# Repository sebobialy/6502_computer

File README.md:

# 6502_computer
Simple 6502 DIY computer for peripheral prototyping

**This is a work in progress. Do not try to manufacture yet.**
# Features
1. 65C02 with selectable speed
2. 6551 UART/ACIA with optional USB support via CH340N
3. 6840 clock chip (with buzzer attached)
4. CPU bus accessible, with several selection signals for various parts of memory
5. SyMon III directly working through UART/USB
6. Simple emulator
7. PCB with all possible markings, memory map, and values
8. Compact form, retro look&feel

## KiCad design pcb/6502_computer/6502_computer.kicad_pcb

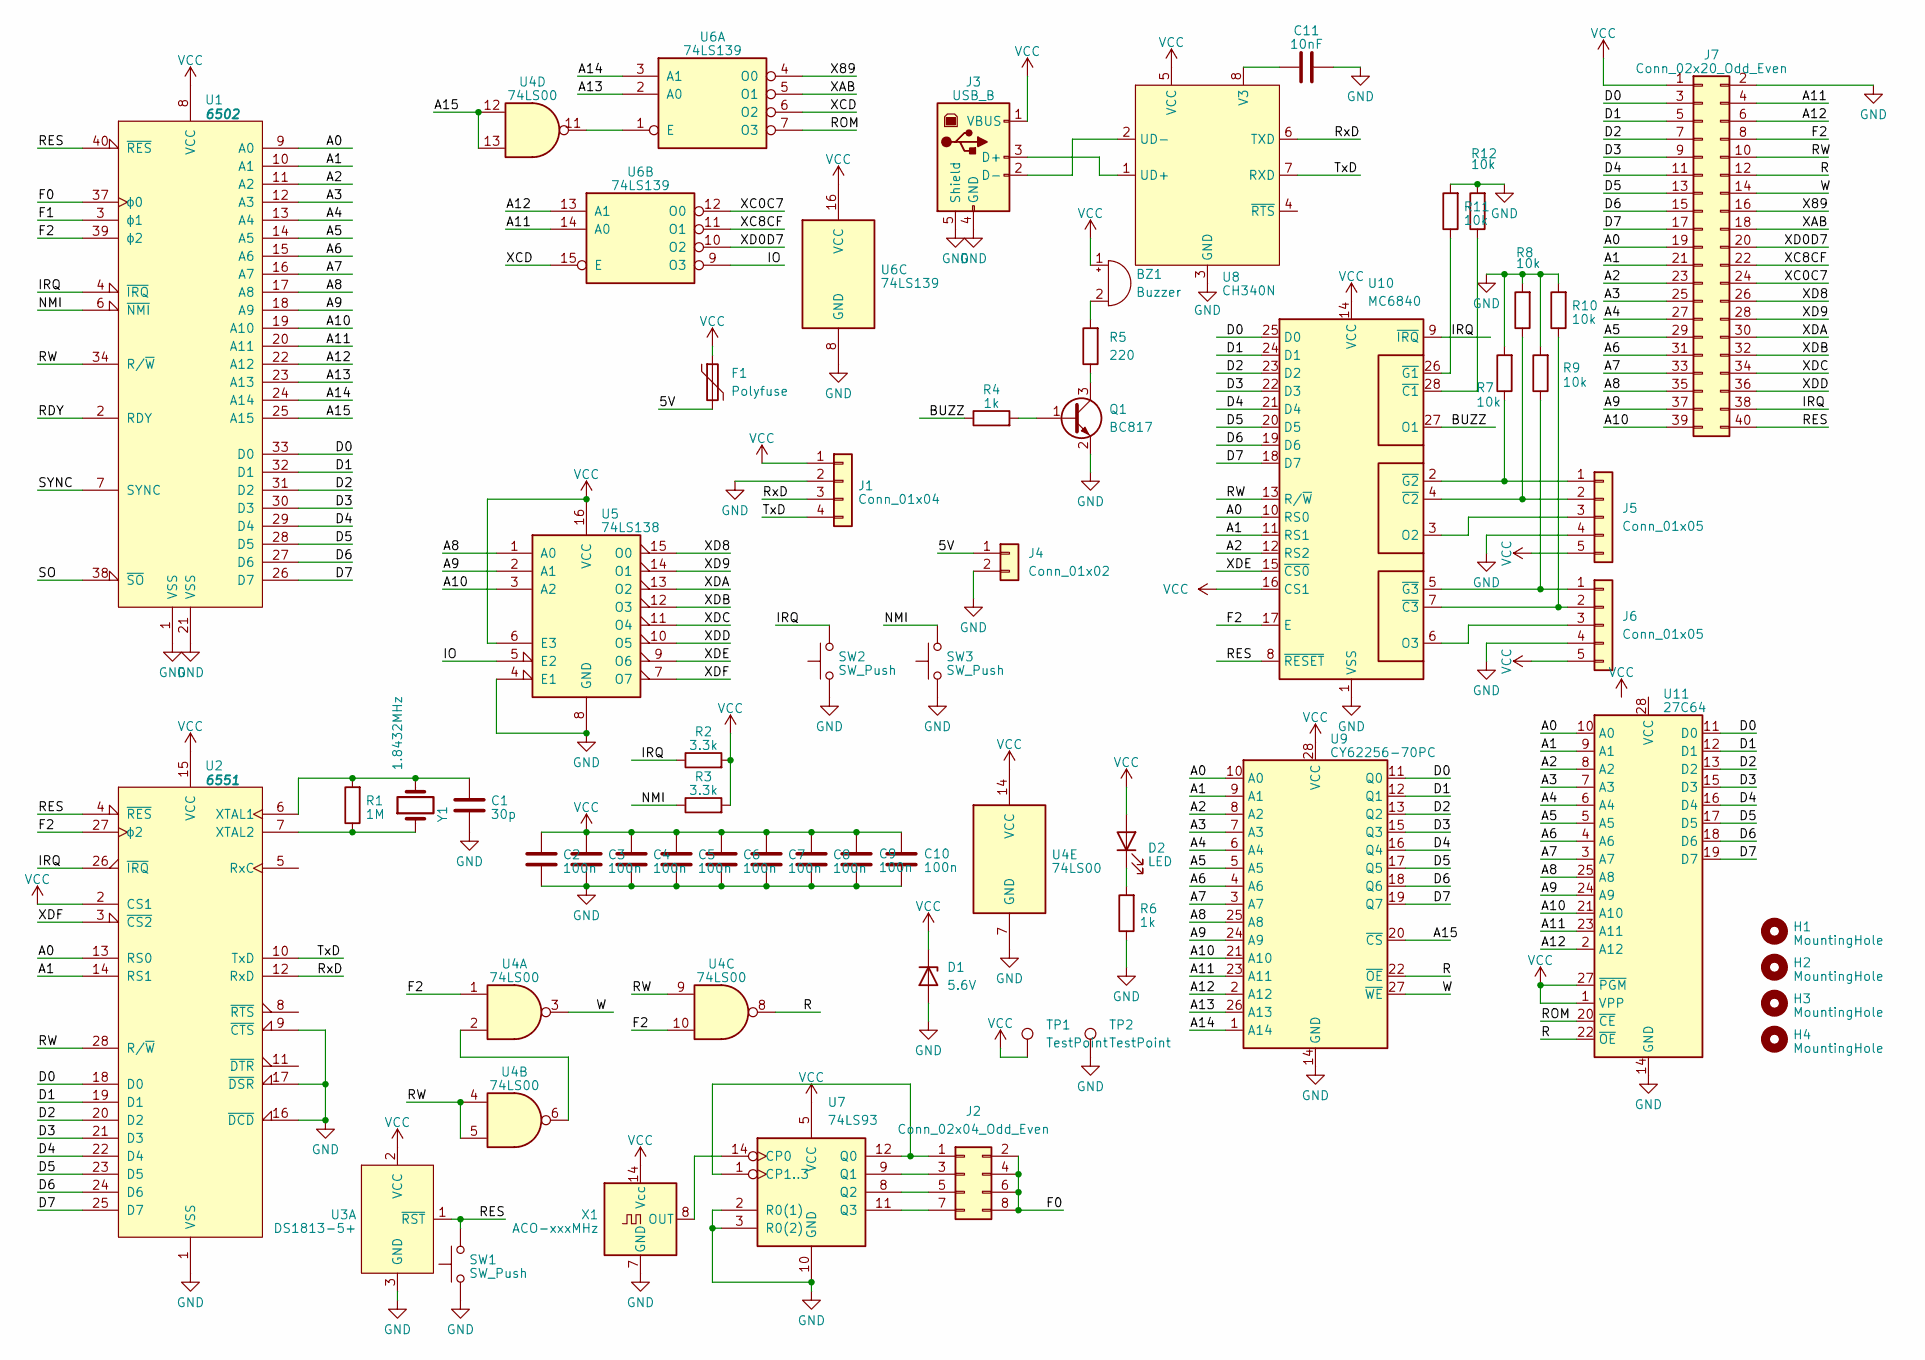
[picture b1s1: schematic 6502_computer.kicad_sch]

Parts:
BZ1: Buzzer; MagneticBuzzer_Kingstate_KCG0601
C1: 30p; C_0805_2012Metric
C2, C3, C4, C5, C6, C7, C8, C9, C10: 100n; C_0805_2012Metric
C11: 10nF; C_0805_2012Metric
D1: 5.6V; D_SOD-123
D2: LED; D_0805_2012Metric
F1: Polyfuse; Fuse_0805_2012Metric
H1, H2, H3, H4: MountingHole; MountingHole_3.2mm_M3
J1: Conn_01x04; Molex_KK-254_AE-6410-04A_1x04_P2.54mm_Vertical
J2: Conn_02x04_Odd_Even; PinHeader_2x04_P2.54mm_Vertical
J3: USB_B; USB_B_Lumberg_2411_02_Horizontal
J4: Conn_01x02; Molex_KK-254_AE-6410-02A_1x02_P2.54mm_Vertical
J5, J6: Conn_01x05; Molex_KK-254_AE-6410-05A_1x05_P2.54mm_Vertical
J7: Conn_02x20_Odd_Even; PinHeader_2x20_P2.54mm_Vertical
Q1: BC817; SOT-23
R1: 1M; R_0805_2012Metric
R2, R3: 3.3k; R_0805_2012Metric
R4, R6: 1k; R_0805_2012Metric
R5: 220; R_0805_2012Metric
R7, R8, R9, R10, R11, R12: 10k; R_0805_2012Metric
SW1, SW2, SW3: SW_Push; SW_PUSH_6mm_H4.3mm
TP1, TP2: TestPoint; PinHeader_1x01_P2.54mm_Vertical
U1: 6502; DIP-40_W15.24mm_LongPads
U2: 6551; DIP-28_W15.24mm_LongPads
U3: DS1813-5+; TO-92
U4: 74LS00; DIP-14_W7.62mm_LongPads
U5: 74LS138; DIP-16_W7.62mm_LongPads
U6: 74LS139; DIP-16_W7.62mm_LongPads
U7: 74LS93; DIP-14_W7.62mm_LongPads
U8: CH340N; SOP-8_3.9x4.9mm_P1.27mm
U9: CY62256-70PC; DIP-28_W15.24mm_LongPads
U10: MC6840; DIP-28_W15.24mm_LongPads
U11: 27C64; DIP-28_W15.24mm_LongPads
X1: ACO-xxxMHz; Oscillator_DIP-14
Y1: 1.8432MHz; Crystal_HC18-U_Horizontal

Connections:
/5V: F1.2, J4.1
/A0: J7.19, U1.9 (A0), U2.13 (RS0), U9.10 (A0), U10.10 (RS0), U11.10 (A0)
/A1: J7.21, U1.10 (A1), U2.14 (RS1), U9.9 (A1), U10.11 (RS1), U11.9 (A1)
/A2: J7.23, U1.11 (A2), U9.8 (A2), U10.12 (RS2), U11.8 (A2)
/A3: J7.25, U1.12 (A3), U9.7 (A3), U11.7 (A3)
/A4: J7.27, U1.13 (A4), U9.6 (A4), U11.6 (A4)
/A5: J7.29, U1.14 (A5), U9.5 (A5), U11.5 (A5)
/A6: J7.31, U1.15 (A6), U9.4 (A6), U11.4 (A6)
/A7: J7.33, U1.16 (A7), U9.3 (A7), U11.3 (A7)
/A8: J7.35, U1.17 (A8), U5.1 (A0), U9.25 (A8), U11.25 (A8)
/A9: J7.37, U1.18 (A9), U5.2 (A1), U9.24 (A9), U11.24 (A9)
/A10: J7.39, U1.19 (A10), U5.3 (A2), U9.21 (A10), U11.21 (A10)
/A11: J7.4, U1.20 (A11), U6.14 (A0), U9.23 (A11), U11.23 (A11)
/A12: J7.6, U1.22 (A12), U6.13 (A1), U9.2 (A12), U11.2 (A12)
/A13: U1.23 (A13), U6.2 (A0), U9.26 (A13)
/A14: U1.24 (A14), U6.3 (A1), U9.1 (A14)
/A15: U1.25 (A15), U4.12, U4.13, U9.20 (~CS)
/BUZZ: R4.1, U10.27 (O1)
/D0: J7.3, U1.33 (D0), U2.18 (D0), U9.11 (Q0), U10.25 (D0), U11.11 (D0)
/D1: J7.5, U1.32 (D1), U2.19 (D1), U9.12 (Q1), U10.24 (D1), U11.12 (D1)
/D2: J7.7, U1.31 (D2), U2.20 (D2), U9.13 (Q2), U10.23 (D2), U11.13 (D2)
/D3: J7.9, U1.30 (D3), U2.21 (D3), U9.15 (Q3), U10.22 (D3), U11.15 (D3)
/D4: J7.11, U1.29 (D4), U2.22 (D4), U9.16 (Q4), U10.21 (D4), U11.16 (D4)
/D5: J7.13, U1.28 (D5), U2.23 (D5), U9.17 (Q5), U10.20 (D5), U11.17 (D5)
/D6: J7.15, U1.27 (D6), U2.24 (D6), U9.18 (Q6), U10.19 (D6), U11.18 (D6)
/D7: J7.17, U1.26 (D7), U2.25 (D7), U9.19 (Q7), U10.18 (D7), U11.19 (D7)
/F0: J2.2, J2.4, J2.6, J2.8, U1.37 (ϕ0)
/F1: U1.3 (ϕ1)
/F2: J7.8, U1.39 (ϕ2), U2.27 (ϕ2), U4.1, U4.10, U10.17 (E)
/IO: U5.5 (E2), U6.9 (O3)
/NMI: R3.1, SW3.2, U1.6 (~NMI)
/R: J7.12, U4.8, U9.22 (~OE), U11.22 (~OE)
/RDY: U1.2 (RDY)
/RES: J7.40, SW1.2, U1.40 (~RES), U2.4 (~RES), U3.1 (~RST), U10.8 (~RESET)
/ROM: U6.7 (O3), U11.20 (~CE)
/RW: J7.10, U1.34 (R/~W), U2.28 (R/~W), U4.4, U4.5, U4.9, U10.13 (R/~W)
/RxD: J1.3, U2.12 (RxD), U8.6 (TXD)
/SO: U1.38 (~SO)
/SYNC: U1.7 (SYNC)
/TxD: J1.4, U2.10 (TxD), U8.7 (RXD)
/W: J7.14, U4.3, U9.27 (~WE)
/X89: J7.16, U6.4 (O0)
/XAB: J7.18, U6.5 (O1)
/XC0C7: J7.24, U6.12 (O0)
/XC8CF: J7.22, U6.11 (O1)
/XCD: U6.6 (O2), U6.15 (E)
/XD0D7: J7.20, U6.10 (O2)
/XD8: J7.26, U5.15 (O0)
/XD9: J7.28, U5.14 (O1)
/XDA: J7.30, U5.13 (O2)
/XDB: J7.32, U5.12 (O3)
/XDC: J7.34, U5.11 (O4)
/XDD: J7.36, U5.10 (O5)
/XDE: U5.9 (O6), U10.15 (~CS0)
/XDF: U2.3 (~CS2), U5.7 (O7)
GND: C1.1, C2.1, C3.1, C4.1, C5.1, C6.1, C7.1, C8.1, C9.1, C10.1, C11.1, D1.2 (A), J1.2, J3.4 (GND), J3.5 (Shield), J4.2, J5.4, J6.4, J7.2, Q1.2 (E), R6.1, R7.2, R8.2, R9.2, R10.2, R11.2, R12.2, SW1.1, SW2.1, SW3.1, TP2.1, U1.1 (VSS), U1.21 (VSS), U2.1 (VSS), U2.9 (~CTS), U2.16 (~DCD), U2.17 (~DSR), U3.3 (GND), U4.7 (GND), U5.4 (E1), U5.8 (GND), U6.8 (GND), U7.2 (R0(1)), U7.3 (R0(2)), U7.10 (GND), U8.3 (GND), U9.14 (GND), U10.1 (VSS), U11.14 (GND), X1.7 (GND)
unnamed: BZ1.2 (-), R5.2
unnamed: D2.1 (K), R6.2
unnamed: J2.1, U7.1 (CP1..3), U7.12 (Q0)
unnamed: J2.3, U7.9 (Q1)
unnamed: J2.5, U7.8 (Q2)
unnamed: J2.7, U7.11 (Q3)
unnamed: J3.3 (D+), U8.1 (UD+)
unnamed: J3.2 (D-), U8.2 (UD-)
unnamed: J5.1, R7.1, U10.2 (~G2)
unnamed: J5.2, R8.1, U10.4 (~C2)
unnamed: J5.3, U10.3 (O2)
unnamed: J6.1, R9.1, U10.5 (~G3)
unnamed: J6.2, R10.1, U10.7 (~C3)
unnamed: J6.3, U10.6 (O3)
unnamed: Q1.1 (B), R4.2
unnamed: Q1.3 (C), R5.1
unnamed: C1.2, R1.2, U2.6 (XTAL1), Y1.2
unnamed: R1.1, U2.7 (XTAL2), Y1.1
unnamed: U4.2, U4.6
unnamed: U4.11, U6.1 (E)
unnamed: U7.14 (CP0), X1.8 (OUT)
unnamed: C11.2, U8.8 (V3)
unnamed: R12.1, U10.28 (~C1)
VCC: BZ1.1 (+), C2.2, C3.2, C4.2, C5.2, C6.2, C7.2, C8.2, C9.2, C10.2, D1.1 (K), D2.2 (A), F1.1, J1.1, J3.1 (VBUS), J5.5, J6.5, J7.1, R2.2, R3.2, TP1.1, U1.8 (VCC), U2.2 (CS1), U2.15 (VCC), U3.2 (VCC), U4.14 (VCC), U5.6 (E3), U5.16 (VCC), U6.16 (VCC), U7.5 (VCC), U8.5 (VCC), U9.28 (VCC), U10.14 (VCC), U10.16 (CS1), U11.1 (VPP), U11.27 (~PGM), X1.14 (Vcc)

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
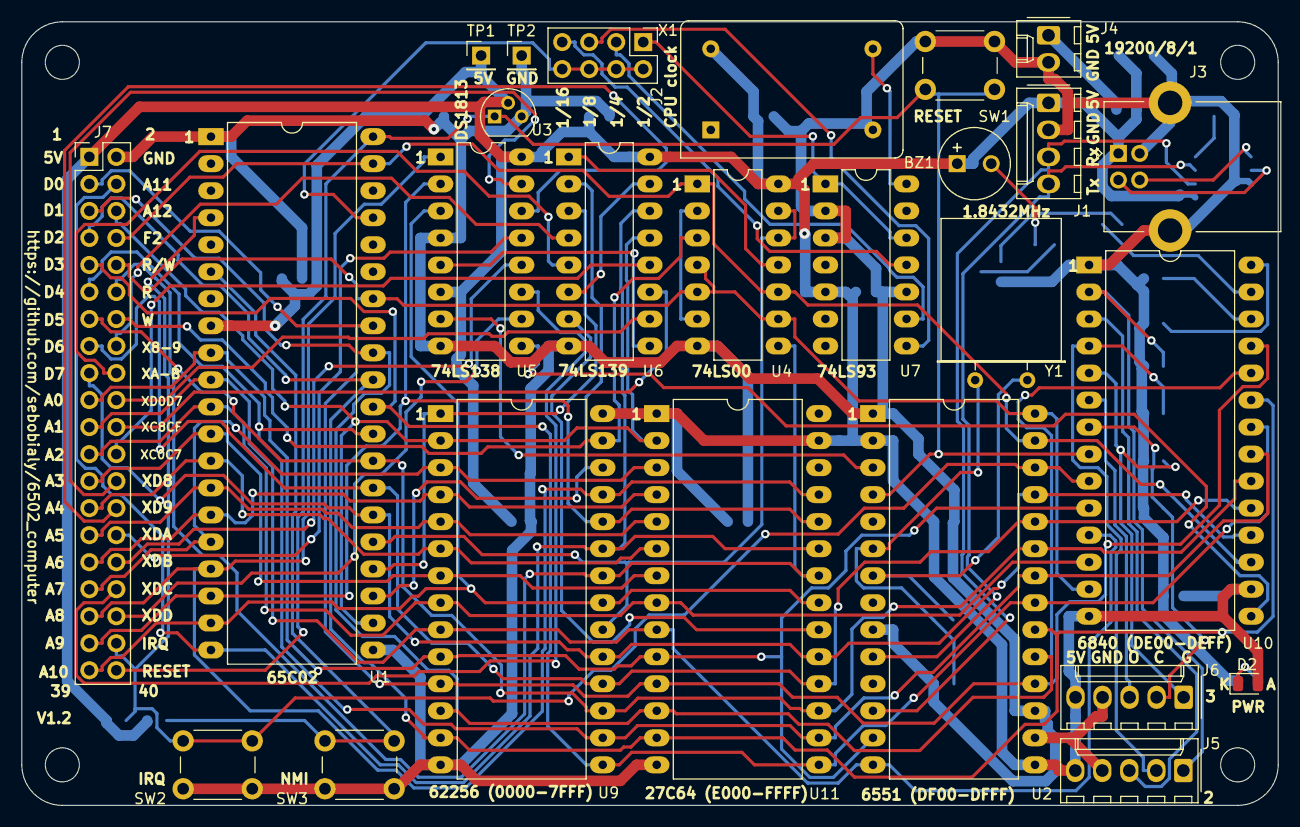
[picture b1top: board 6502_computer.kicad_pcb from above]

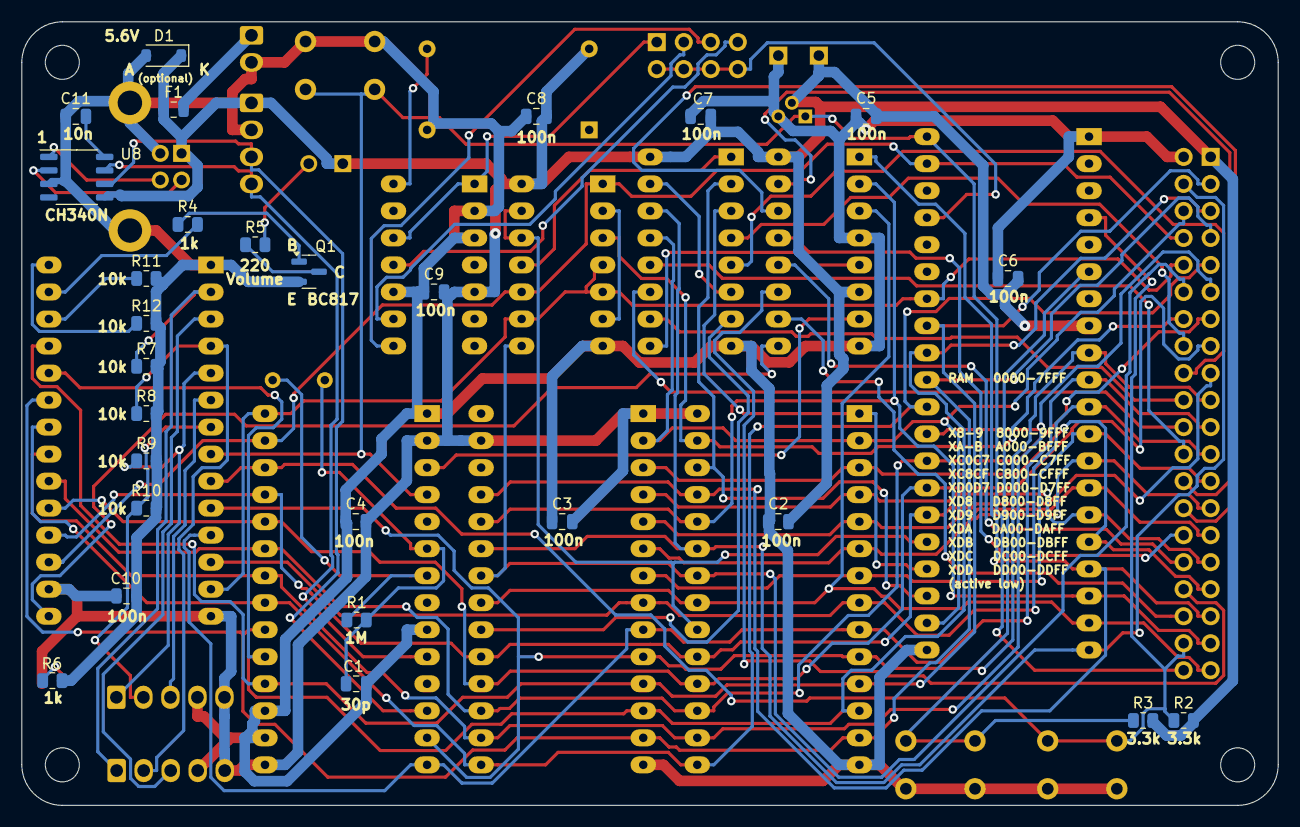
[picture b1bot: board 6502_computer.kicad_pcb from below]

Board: 2 copper layers, 118.1 x 73.7 mm, 57 parts (27 on the bottom side), 78 nets.

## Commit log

2024-04-06 Added emulator files
2024-04-06 readme updated
2024-04-07 silkscreen fixes
2024-04-09 added timer outputs from 6840
2024-04-09 3d view updated
2024-10-07 fixed problem with not negating E for 74LS139. Buzzer is now using a transistor. 6502 is ZIF friendly.
2024-10-08 routed 1.2 version
2024-10-11 routed v1.2
2024-10-15 vscode workspace
2024-10-15 tasks for vscode
2024-10-15 +x for sript
2024-10-15 build system reorganized
2024-10-26 v1.2 label fixes, pullup resistors for uart, routed
